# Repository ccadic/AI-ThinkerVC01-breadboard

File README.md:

# AI-ThinkerVC01-breadboard
Developpement board for the AI Thinker Voice CHIP VC01
GPL3 licence - @sulfuroid

All files: 3D solidworks, STEP 3D
Foootprint and KICAD 5.x Lib

And a basic breadboard PCB to test

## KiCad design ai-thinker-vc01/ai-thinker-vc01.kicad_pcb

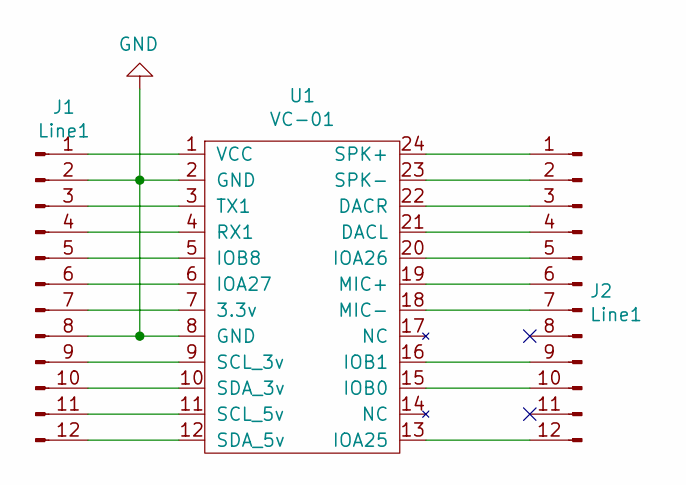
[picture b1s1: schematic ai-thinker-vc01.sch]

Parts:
J1, J2: Line1; PinHeader_1x12_P2.54mm_Vertical
U1: VC-01; AI-Thinker-VC01

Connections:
GND: J1.2, J1.8, U1.2 (GND), U1.8 (GND)
unnamed: J1.1, U1.1 (VCC)
unnamed: J1.3, U1.3 (TX1)
unnamed: J1.4, U1.4 (RX1)
unnamed: J1.5, U1.5 (IOB8)
unnamed: J1.6, U1.6 (IOA27)
unnamed: J1.7, U1.7 (3.3v)
unnamed: J1.9, U1.9 (SCL_3v)
unnamed: J1.10, U1.10 (SDA_3v)
unnamed: J1.11, U1.11 (SCL_5v)
unnamed: J1.12, U1.12 (SDA_5v)
unnamed: J2.1, U1.24 (SPK+)
unnamed: J2.2, U1.23 (SPK-)
unnamed: J2.3, U1.22 (DACR)
unnamed: J2.4, U1.21 (DACL)
unnamed: J2.5, U1.20 (IOA26)
unnamed: J2.6, U1.19 (MIC+)
unnamed: J2.7, U1.18 (MIC-)
unnamed: J2.9, U1.16 (IOB1)
unnamed: J2.10, U1.15 (IOB0)
unnamed: J2.12, U1.13 (IOA25)

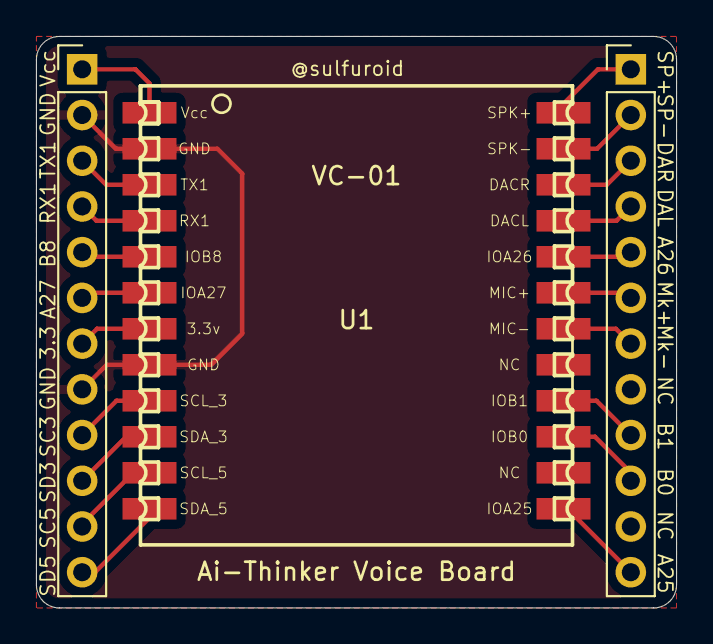
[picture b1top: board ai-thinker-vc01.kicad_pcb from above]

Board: 2 copper layers, 35.6 x 31.8 mm, 3 parts (0 on the bottom side), 21 nets.
